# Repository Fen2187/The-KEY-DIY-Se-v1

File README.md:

**Why this exsits:**This keyboard was made for fun and for portability. This was an idea I got. It has no firmware, only the pcb file. If it is built pls show or credit at least.

Note to open and edit things like the PCB and case you may need CAD software and or software that can open standard pcb files.

There is not firmware this is up to users prefrence as well as users dessision. 

Have fun buildingh and mess around. It was fun making.

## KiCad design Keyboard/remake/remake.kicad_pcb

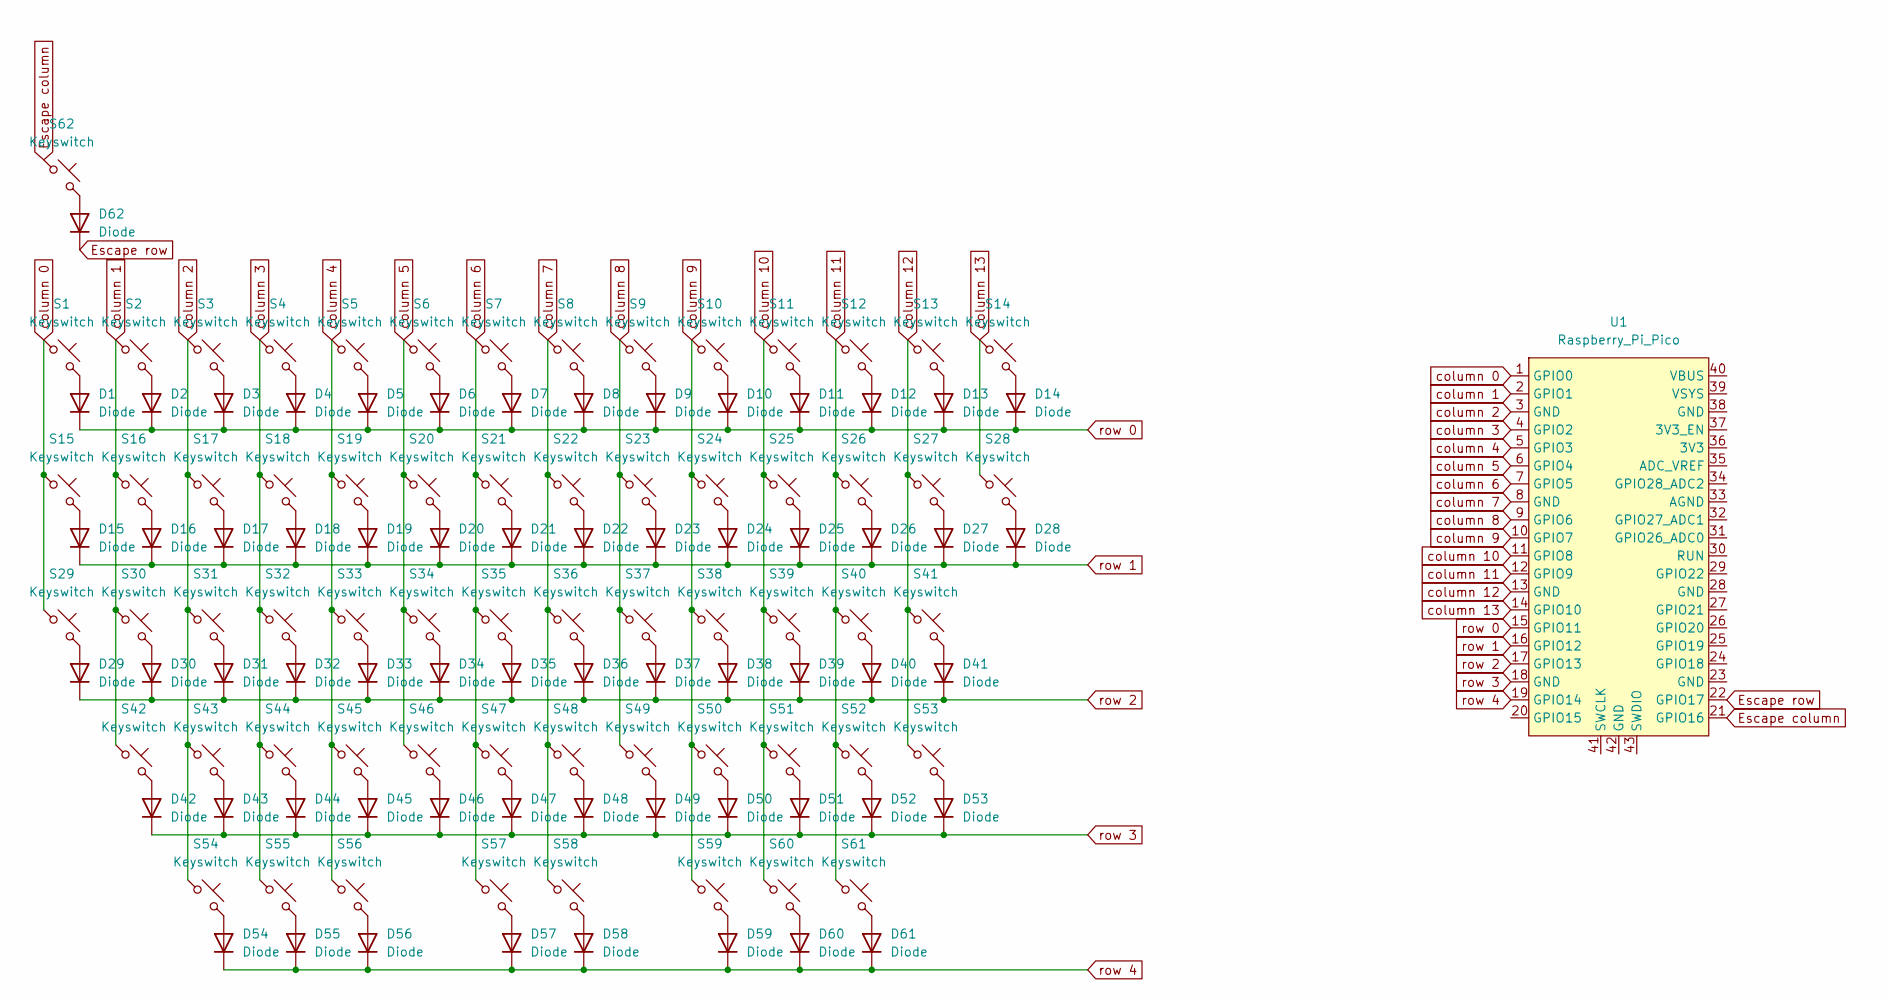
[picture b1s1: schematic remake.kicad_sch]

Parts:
D1, D2, D3, D4, D5, D6, D7, D8, D9, D10, D11, D12, D13, D14, D15, D16, D17, D18, D19, D20, D21, D22, D23, D24, D25, D26, D27, D28, D29, D30, D31, D32, D33, D34, D35, D36, D37, D38, D39, D40, D41, D42, D43, D44, D45, D46, D47, D48, D49, D50, D51, D52, D53, D54, D55, D56, D57, D58, D59, D60, D61, D62: Diode; Diode_DO-35
S1, S2, S3, S4, S5, S6, S7, S8, S9, S10, S11, S12, S13, S14, S15, S16, S17, S18, S19, S20, S21, S22, S23, S24, S25, S26, S27, S28, S29, S30, S31, S32, S33, S34, S35, S36, S37, S38, S39, S40, S41, S42, S43, S44, S45, S46, S47, S48, S49, S50, S51, S52, S53, S54, S55, S56, S57, S58, S59, S60, S61, S62: Keyswitch; MX_PCB_1.00u
U1: Raspberry_Pi_Pico

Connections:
Escape column: S62.1, U1.21 (GPIO16)
Escape row: D62.1 (K), U1.22 (GPIO17)
unnamed: D1.2 (A), S1.2
unnamed: D2.2 (A), S2.2
unnamed: D3.2 (A), S3.2
unnamed: D4.2 (A), S4.2
unnamed: D5.2 (A), S5.2
unnamed: D6.2 (A), S6.2
unnamed: D7.2 (A), S7.2
unnamed: D8.2 (A), S8.2
unnamed: D9.2 (A), S9.2
unnamed: D10.2 (A), S10.2
unnamed: D11.2 (A), S11.2
unnamed: D12.2 (A), S12.2
unnamed: D13.2 (A), S13.2
unnamed: D14.2 (A), S14.2
unnamed: D15.2 (A), S15.2
unnamed: D16.2 (A), S16.2
unnamed: D17.2 (A), S17.2
unnamed: D18.2 (A), S18.2
unnamed: D19.2 (A), S19.2
unnamed: D20.2 (A), S20.2
unnamed: D21.2 (A), S21.2
unnamed: D22.2 (A), S22.2
unnamed: D23.2 (A), S23.2
unnamed: D24.2 (A), S24.2
unnamed: D25.2 (A), S25.2
unnamed: D26.2 (A), S26.2
unnamed: D27.2 (A), S27.2
unnamed: D28.2 (A), S28.2
unnamed: D29.2 (A), S29.2
unnamed: D30.2 (A), S30.2
unnamed: D31.2 (A), S31.2
unnamed: D32.2 (A), S32.2
unnamed: D33.2 (A), S33.2
unnamed: D34.2 (A), S34.2
unnamed: D35.2 (A), S35.2
unnamed: D36.2 (A), S36.2
unnamed: D37.2 (A), S37.2
unnamed: D38.2 (A), S38.2
unnamed: D39.2 (A), S39.2
unnamed: D40.2 (A), S40.2
unnamed: D41.2 (A), S41.2
unnamed: D42.2 (A), S42.2
unnamed: D43.2 (A), S43.2
unnamed: D44.2 (A), S44.2
unnamed: D45.2 (A), S45.2
unnamed: D46.2 (A), S46.2
unnamed: D47.2 (A), S47.2
unnamed: D48.2 (A), S48.2
unnamed: D49.2 (A), S49.2
unnamed: D50.2 (A), S50.2
unnamed: D51.2 (A), S51.2
unnamed: D52.2 (A), S52.2
unnamed: D53.2 (A), S53.2
unnamed: D54.2 (A), S54.2
unnamed: D55.2 (A), S55.2
unnamed: D56.2 (A), S56.2
unnamed: D57.2 (A), S57.2
unnamed: D58.2 (A), S58.2
unnamed: D59.2 (A), S59.2
unnamed: D60.2 (A), S60.2
unnamed: D61.2 (A), S61.2
unnamed: D62.2 (A), S62.2
column 0: S1.1, S15.1, S29.1, U1.1 (GPIO0)
column 1: S2.1, S16.1, S30.1, S42.1, U1.2 (GPIO1)
column 2: S3.1, S17.1, S31.1, S43.1, S54.1, U1.3 (GND)
column 3: S4.1, S18.1, S32.1, S44.1, S55.1, U1.4 (GPIO2)
column 4: S5.1, S19.1, S33.1, S45.1, S56.1, U1.5 (GPIO3)
column 5: S6.1, S20.1, S34.1, S46.1, U1.6 (GPIO4)
column 6: S7.1, S21.1, S35.1, S47.1, S57.1, U1.7 (GPIO5)
column 7: S8.1, S22.1, S36.1, S48.1, S58.1, U1.8 (GND)
column 8: S9.1, S23.1, S37.1, S49.1, U1.9 (GPIO6)
column 9: S10.1, S24.1, S38.1, S50.1, S59.1, U1.10 (GPIO7)
column 10: S11.1, S25.1, S39.1, S51.1, S60.1, U1.11 (GPIO8)
column 11: S12.1, S26.1, S40.1, S52.1, S61.1, U1.12 (GPIO9)
column 12: S13.1, S27.1, S41.1, S53.1, U1.13 (GND)
column 13: S14.1, S28.1, U1.14 (GPIO10)
row 0: D1.1 (K), D2.1 (K), D3.1 (K), D4.1 (K), D5.1 (K), D6.1 (K), D7.1 (K), D8.1 (K), D9.1 (K), D10.1 (K), D11.1 (K), D12.1 (K), D13.1 (K), D14.1 (K), U1.15 (GPIO11)
row 1: D15.1 (K), D16.1 (K), D17.1 (K), D18.1 (K), D19.1 (K), D20.1 (K), D21.1 (K), D22.1 (K), D23.1 (K), D24.1 (K), D25.1 (K), D26.1 (K), D27.1 (K), D28.1 (K), U1.16 (GPIO12)
row 2: D29.1 (K), D30.1 (K), D31.1 (K), D32.1 (K), D33.1 (K), D34.1 (K), D35.1 (K), D36.1 (K), D37.1 (K), D38.1 (K), D39.1 (K), D40.1 (K), D41.1 (K), U1.17 (GPIO13)
row 3: D42.1 (K), D43.1 (K), D44.1 (K), D45.1 (K), D46.1 (K), D47.1 (K), D48.1 (K), D49.1 (K), D50.1 (K), D51.1 (K), D52.1 (K), D53.1 (K), U1.18 (GND)
row 4: D54.1 (K), D55.1 (K), D56.1 (K), D57.1 (K), D58.1 (K), D59.1 (K), D60.1 (K), D61.1 (K), U1.19 (GPIO14)

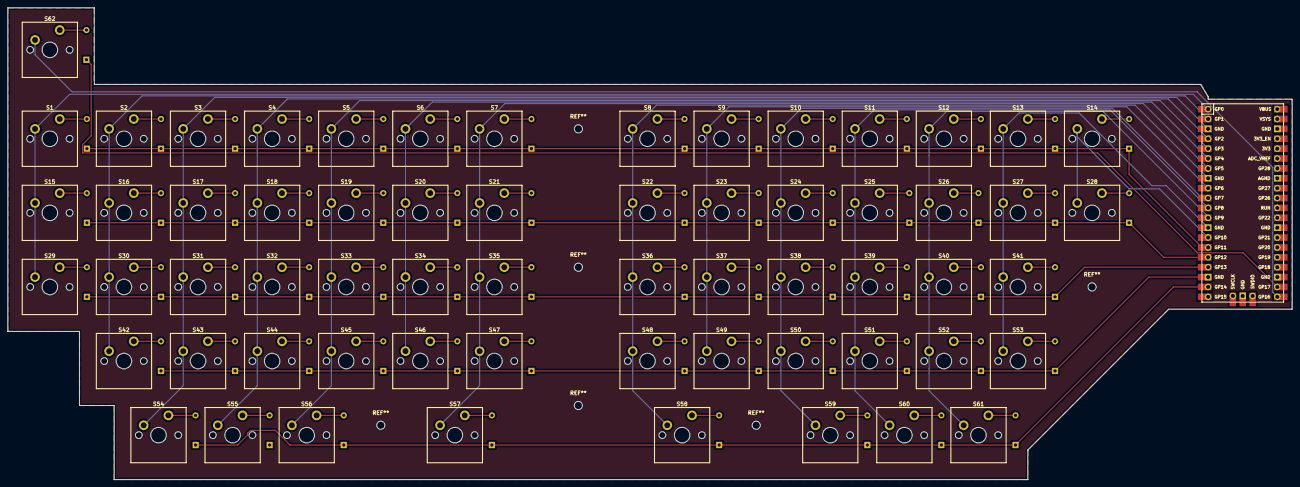
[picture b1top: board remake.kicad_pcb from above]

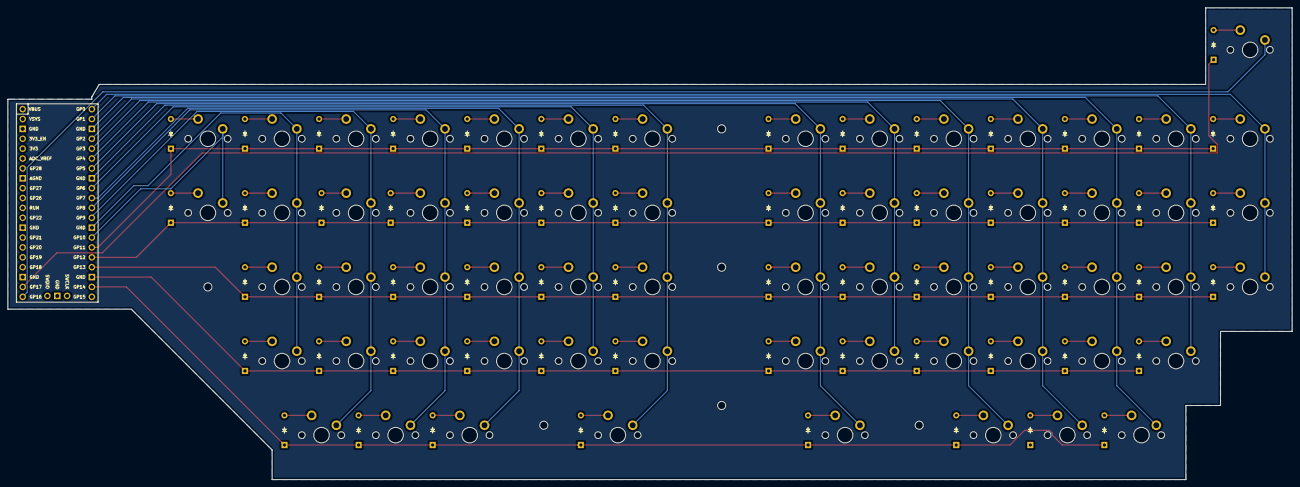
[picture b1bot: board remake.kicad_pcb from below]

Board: 2 copper layers, 330.2 x 121.3 mm, 125 parts (62 on the bottom side), 83 nets.

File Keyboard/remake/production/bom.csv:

Designator,Footprint,Quantity,Value,LCSC Part #
"D1, D10, D11, D12, D13, D14, D15, D16, D17, D18, D19, D2, D20, D21, D22, D23, D24, D25, D26, D27, D28, D29, D3, D30, D31, D32, D33, D34, D35, D36, D37, D38, D39, D4, D40, D41, D42, D43, D44, D45, D46, D47, D48, D49, D5, D50, D51, D52, D53, D54, D55, D56, D57, D58, D59, D6, D60, D61, D62, D7, D8, D9",Diode_DO-35,62,Diode,
"S1, S10, S11, S12, S13, S14, S15, S16, S17, S18, S19, S2, S20, S21, S22, S23, S24, S25, S26, S27, S28, S29, S3, S30, S31, S32, S33, S34, S35, S36, S37, S38, S39, S4, S40, S41, S42, S43, S44, S45, S46, S47, S48, S49, S5, S50, S51, S52, S53, S54, S55, S56, S57, S58, S59, S6, S60, S61, S62, S7, S8, S9",MX_PCB_1.00u,62,Keyswitch,
U1,Raspberry_Pi_Pico,1,Raspberry_Pi_Pico,

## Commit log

2024-11-17 My dream is gone
2025-02-11 README.md
2025-03-09 The keyboard
    This is the files for printing and making of the pcb and case.
